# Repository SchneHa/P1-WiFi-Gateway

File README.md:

### P1-WiFi-Gateway
P1-WiFi-Gateway mit Unterstützung der cFos Power Brain Wallbox

P1 wifi gateway 2022

**(English Version below)**

Basierend auf einem Repo von Ronald Leenes: https://github.com/romix123/P1-wifi-gateway

Diese Software vereint verschiedene Komponenten in einem handlichen Paket.
Die Software läuft auf einem ESP8266 board wie dem Wemos D1 mini oder mini Pro und hat einen bescheidenen Platzbedarf.

Die Datenverarbeitung basiert auf: http://domoticx.com/p1-poort-smart-meter-data-to-domoticz-esp8266 
Das Captive Portal basiert auf einem der ESP8266-Beispiele, die OTA-Einheit ebenfalls.

Das Modul liefert Daten über JSON- oder MQTT-Nachrichten an einen Host, kann aber auch über das Webinterface des Moduls oder per Telnet ausgelesen werden. Die Daten können an einen virtuellen Zähler "HTTP input" in der Power Brain Wallbox von cFos übertragen werden und dort für das Lastmanagement genutzt werden. Damit das funktioniert, muss der Charging Manager der Wallbox mindestens auf die Firmwareversion 1.17.4-beta gebracht werden.

Das Modul lädt beim Start zuerst den Pufferkondensator auf. Es blinkt dann 2x und versucht zunächst, sich mit Ihrem WLAN-Netzwerk zu verbinden. Während dieses Vorgangs blinkt die LED mit einer Periode von 0,5 Hz. Kommt keine Verbindung zustande, startet das Modul einen Access Point mit dem Namen P1_Setup. Verbinden Sie sich mit diesem Netzwerk und surfen Sie zu 192.168.4.1

Daraufhin erscheint der Menübildschirm des Moduls. Geben Sie dort die SSID und das Passwort Ihres WLAN-Netzwerks ein. Darunter tragen Sie die Daten des empfangenden Servers (IP und Portnummer) ein. Dies kann Ihr Domotociz-Server sein, in diesem Fall müssen Sie auch die IDx eingeben, die Domoticz für ein Gas- und ein Energiegerät erstellt. 
Auch die Daten für einen (z. B. auf einem Raspberry Pi selbst gehosteten) MQTT-Broker können jetzt eingegeben werden.

Wenn die Daten für das Lastmanagement einer cFos Power Brain Wallbox genutzt werden sollen, ist dies ebenfalls hier möglich.

In der jetzt veröffentlichten Version 1.2f ist es nun auch möglich, Gas-Verbrauchswerte über MQTT zu empfangen, die von einem Gassensor wie in meinem Repo https://github.com/SchneHa/Gas_Meter beschrieben gesendet werden. Es werden im Webinterface des P1-Gateways der Gas-Gesamtzähler und der aktuelle Tageszähler dargestellt. Dafür kann derselbe Broker wie für die anderen Werte angegeben werden, es kann aber auch ein anderer Broker sein.

Schließlich geben Sie an, wie viele Sekunden Daten an den Server gesendet werden sollen. DSMR4-Messgeräte verwenden ein Messintervall von 10 Sekunden. SMR5-Zähler liefern jede Sekunde Daten. Das erscheint  viel und das Modul benötigt auch viel Strom, daher ist die Frage, ob es parasitär (powered by the meter) arbeiten kann. Empfohlen ist  ein Intervall von 15 Sekunden oder höher. Das hier eingegebene Intervall wird nicht immer synchron zum Datenintervall des Zählers sein, gehen Sie also nicht davon aus, dass Sie in Domoticz, MQTT oder im Charging Manager der cFos Wallbox  genau alle x Sekunden einen Messwert sehen. 

Das Modul „schläft“ zwischen den Messungen (das Modem wird ausgeschaltet, so dass die Stromaufnahme von ca. 70 mA auf 15 mA sinkt). Dies gibt dem Pufferkondensator Zeit, sich für die vom WLAN-Sender des Moduls erzeugten Stromspitzen aufzuladen (und es spart dennoch etwas Strom (der von Ihrem Energieversorger bezahlt wird, aber trotzdem)). Jedes bisschen hilft.

Siehe http://esp8266thingies.nl für weitere Informationen über das Modul und http://www.esp8266thingies.nl/wp/forum-2/ für das Diskussionsforum.

Ergänzung vom 31.07.2023: Seit heute sind die PCB Dateien im KiCAD Format online. Das Board wurde schon produziert und getestet. Ebenso stehen die Gerber Dateien zur Verfügung.

Ich habe noch einige PCBs aus der ersten Produktion übrig, bei Bedarf bitte melden.
```
PCB unbestückt: 5€
PCB mit Bauteilen: 10€
PCB fertig bestückt: 15€
D1 mini ESP8266 mit Headern: 10€
inklusive Versand innerhalb Deutschlands
hans(dot)schneider(at)gmx(dot)ch
```

```
Version: 1.2f Datum: 29. Mai 2026
         Gasverbrauch (Gesamtzähler und Tageszähler), Import der Werte über MQTT implementiert
         Voraussetzung: Vorhandensein eines Gas-Sensors wie unter meinem Repo
         https://github.com/SchneHa/Gas_Meter beschrieben
Version: 1.2e Datum: 02.11.2025
         Checkt nun in jedem loop, ob eine Verbindung zum WiFi besteht. Wenn nicht, wird die
         Verbindung neu hergestellt.
Version: 1.2d Datum: 15.01.2025
         nach Ändern des voreingestellten Passworts für die cFos Power Brain wird das Passwort
         nun nicht mehr vergessen
Version: 1.2c Datum: 23.05.2024
         die Anzeige der Seite mit den Messwerten wird nun alle 20 Sekunden erneuert
         P1meter sendet nun positive Werte für actualElectricityPowerDelivered und negative Werte
         für actualElectricityPowerReturned zur cFos Power Brain Wallbox (das ist wichtig um
         korrekte Werte für die Einspeisung ins Stomnetz zu erhalten)
Version: 1.2b Datum: 22.05.2023
         Anpassungen für die Firmware 1.19.4 der cFos Power Brain Wallbox
         (power_va ist nun power_w, is_va existiert nicht mehr)
         Korrekturen der niederländischen, französischen und schwedischen Version
Version: 1.2a Datum: 13.03.2023
         Fertigstellung der französischen und schwedischen Version
         diverse Verbesserungen und Fehlerbehebungen
Version: 1.2 Datum: 05.03.2023, Autor: Hans Schneider
         Unterstützung für den HTTP_input Zähler der cFos Power Brain Wallbox hinzugefügt
         diverse Verbesserungen und Fehlerbehebungen
Version: 1.1adc Datum: 12.02.2023 Autor: Ronald Leenes
1.1adc: Umfangreiche Protokollierung implementiert
        Schwedische Version aktualisiert, um sie an die niederländische Version anzugleichen 
        (Deutsche und Französische Version haben keine Sicherheitsfunktionen bei Setup/Update)
1.1aa: Fehlerkorrekturen 1.1: Graphen implementiert BerichtstarifIndicatorElectricity behoben
ud: Kopfzeilen aktualisieren behoben ua: Problem mit Setup-Feldern behoben
u: Passwortschutz für Setup- und Update-Firmware-Menüs hinzugefügt
   Gehen Sie beim ersten Booten von Version 1.0u innerhalb von 60 Sekunden zum Setup-Menü, um den
   Passwortschutz zu umgehen
   Out-of-the-Box-Unterstützung für die Integration von Home Assistant "DSMR Reader" hinzugefügt 
   Verwenden Sie „dsmr“ als MQTT-Präfix und Daten werden automatisch im „DSMR Reader“-Format an den
   MQTT-Broker geliefert
   MQTT-Wiederverbindung behoben, es ist jetzt nicht blockierend
   Zurücksetzen der Hardboot-Tageszähler behoben
   Senden leerer MQTT-Nachrichten behoben
   Insgesamt verbesserte Stabilität
t: Verbesserungen bei der Energieverwaltung
   allgemeine (kleinere) Bereinigung
ta: Korrektur für Telnet-Berichte
    französische Lokalisierung hinzugefügt
s: deutsche Lokalisierung hinzugefügt 
   mqtt-Ausgabe für schwedische spezifische OBIS-Codes hinzugefügt
r: Geschwindigkeitsverbesserungen und Rationalisierung der Parser-Lokalisierungen für: NL, SE
q: Tageswerte hinzugefügt 
p: EquipmentID in mqtt set eingebaut 
o: fixe Gasleistung, fixes mqtt reconnect 
n: leerer Aufruf von SetupSave leitet jetzt zum Hauptmenü weiter statt Einstellungen zurückzusetzen ;-)
   behobene kWh/Wh Invertierung 
m: setupsave fix, relocate to p1wifi.local nach 60 Sek. mqtt 
   kw/W fix 
l: wifireconnect nach WLAN-Verlust 
k: großer BUG behoben, SoftAP würde keinen erreichbaren Webserver erzeugen 
j: Rohdaten auf Port 23
   Hauptcodeumschreibung 
   implementierte Datenberichtsmethoden: geparste Daten: json, mqtt, p1wifi.local/P1 
   Rohdaten: Telnet auf Port 23, p1wifi.local/Data
i: erweiterte maximale Leitungslänge für TD210-D-Zähler, die eine wirklich lange 1-0:99.97.0-Leitung haben 
h: erweitertes mqtt-Set mit sofortigen Leistungen, Spannungen, aktueller Tarifgruppe 
   Stromausfälle, Stromabfälle 
g: feste mqtt
```

Empfohlenes Board:

Wemos D1 mini Pro, Flash Größe: 16 MB, FS: 14 MB, OTA: ~1019 kB

ebenso möglich:

Wemos D1 R2 & mini, Flash Größe: 4 MB, FS: 2 MB, OTA: ~1019 kB oder jedes andere kompatible board

```
Benötigte Dateien:
  P1WG2022current.ino
  CRC16.h 
  JSON.ino 
  MQTT.ino 
  TELNET.ino 
  debug.ino 
  decoder.ino 
  functions.ino 
  graph.ino
  logging.ino
  vars.h
  webserver.ino
  webserverDE.ino
  webserverFR.ino
  webserverNL.ino
  webserverSE.ino
  wifi.ino
```
Anmerkung: <Del>Zurzeit sind nur die deutsche und die niederländische Versionen lauffähig.</Del> Bei der französischen und der schwedischen Version muss ggf. die Übersetzung korrigiert werden.

**English Version:**

P1-WiFi-Gateway with support for cFos Power Brain Wallbox

P1 wifi gateway 2022

Based on a repo of Ronald Leenes: https://github.com/romix123/P1-wifi-gateway

This software combines various components in one handy package.
The software runs on an ESP8266 board like the Wemos D1 mini or mini Pro and has a modest footprint.

The data processing is based on: http://domoticx.com/p1-poort-smart-meter-data-to-domoticz-esp8266
The captive portal is based on one of the ESP8266 samples, as is the OTA unit.

The module delivers data to a host via JSON or MQTT messages, but can also be read out via the module's web interface or via Telnet. It is possible to send data to a virtual meter "HTTP input" of the Power Brain Wallbox of cFos which can be used to implement load management. For that to work Charging Manager of cFos Power Brain Wallbox has to be at least on firmware version 1.17.4-beta.

When starting, the module first charges the buffer capacitor. It will then blink 2x and first try to connect to your WiFi network. During this process, the LED flashes with a period of 0.5 Hz. If no connection is established, the module starts an access point with the name P1_Setup. Connect to this network and surf to 192.168.4.1

The module menu screen appears. Enter the SSID and password of your WiFi network there. Below this, enter the data of the receiving server (IP and port number). This can be your Domotociz server, in this case you also have to enter the IDx that Domoticz creates for a gas and an energy device.
The data for an MQTT broker (e.g. hosted on a Raspberry Pi itself) can now also be entered.

If the data is to be used for load management of a cFos Power Brain Wallbox, this is also possible here.

In the newly released version 1.2f, it is now also possible to receive gas consumption data via MQTT, sent by a gas sensor as described in my repository https://github.com/SchneHa/Gas_Meter. The total gas meter reading and the current daily meter reading are displayed in the P1 gateway's web interface. The same broker used for the other values ​​can be specified for this, or a different broker can be used.

Finally, specify how many seconds of data should be sent to the server. DSMR4 gauges use a measurement interval of 10 seconds. SMR5 counters provide data every second. That seems a lot to me and the module also draws a lot of current, so the question is whether it can operate parasitically (powered by the meter). I recommend an interval of 15 seconds or higher. The interval entered here will not always be in sync with the meter's data interval, so don't assume that you will see a reading in Domoticz, MQTT or in Charging Manager of the cFos Wallbox exactly every x seconds. 

The module "sleeps" between the measurements (the modem is switched off so that the current consumption drops from approx. 70 mA to 15 mA). This gives the buffer capacitor time to charge up for the current spikes generated by the module's WiFi transmitter (and it still saves some electricity (which is paid for by your utility, but still)). Every little helps.

See http://esp8266thingies.nl for more information about the module and http://www.esp8266thingies.nl/wp/forum-2/ for the discussion forum.

Addition from 07/31/2023: Since today the PCB files in KiCAD format are online. The board has already been produced and tested. The Gerber files are also available.

I still have some PCBs left from the first batch, please let me know if you need one.

```
PCB unassembled: 5€
PCB with parts: 10€
PCB assembled: 15€
D1 mini ESP8266 with headers: 10€
shipping to Germany included
hans(dot)schneider(at)gmx(dot)ch
```

```
Version: 1.2f Date: 29.5.2026
         Gas consumption (Total counter and daily counter), import of the values via MQTT implemented
         Requirement: A Gas sensor as described in my repo https://github.com/SchneHa/Gas_Meter must
         be available
Version: 1.2e Date: 02.11.2025
         now checks connection to wifi in every loop, if not connected it will be reconnected
Version: 1.2d Date: 15.01.2025
         after changing cFos Power Brain password from it's default the new password isn't forgotten anymore now
Version: 1.2c Date: 23.05.2024
         measurement page refreshes every 20 seconds now
         P1meter now sends positive values for actualElectricityPowerDelivered and negative values for
         actualElectricityPowerReturned to cFos Power Brain wallbox (that is important to calculate correct
         values for feeding energy into the power grid)
Version: 1.2b Date: 22.05.2023
         changes for cFos Power Brain Firmware 1.19.4
         (power_va is now power_w, is_va doesn't exist anymore)
         improvements of dutch, french and swedish language
Version: 1.2a Date: 13.03.2023
         Finishing the french and swedish Version
         various Improvements and bug fixes
Version: 1.2 Date: 03/05/2023, Author: Hans Schneider
         added Support for the HTTP_input meter of cFos Power Brain Wallbox
         various improvements and bug fixes
Version: 1.1adc Date: 02/12/2023 Author: Ronald Leenes
1.1adc: Extensive logging implemented
        Swedish version updated to match Dutch version 
        (German and French versions have no security features on setup/update)
1.1aa: Bug fixes 1.1: Graphs implemented
       Reporting TariffIndicatorElectricity fixed
ud: fixed update headers 
ao: fixed problem with setup fields
u: Added password protection for setup and update firmware menus when booting version 
1.0u for the first time, go to setup menu within 60 seconds to bypass password protection
     Added out-of-the-box support for Home Assistant "DSMR Reader" integration 
     Use "dsmr" as MQTT prefix and data is automatically delivered to the MQTT broker in "DSMR Reader" format
     Fixed MQTT reconnection, it's non-blocking now
     Fixed resetting hardboot day counters
     Fixed sending empty MQTT messages
     Improved overall stability
t: Power management improvements
   general (minor) cleanup 
ta: Fix for telnet reports
    added French localization
s: added german localization
   added mqtt output for swedish specific OBIS codes
r: Speed improvements and streamlining of parser 
   localizations for: NL, SE
q: daily values added 
p: EquipmentID built into mqtt set 
o: fixed gas power
   fixed mqtt reconnect 
n: empty call to SetupSave now redirects to main menu instead of resetting settings ;-)
   fixed kWh/Wh inversion 
m: setupsave fix, relocate to p1wifi.local after 60 sec. 
   mqtt - kw/W fix 
l: wifi reconnect after WLAN loss 
k: major BUG fixed
   SoftAP would not create an accessible web server 
j: raw data on port 23 
   main code rewrite
   implemented data reporting methods: parsed data: json, mqtt, p1wifi.local/P1 
   raw data: telnet on port 23, p1wifi.local/Data
i: extended maximum line length for TD210-D meters that have a really long 1-0:99.97.0 line 
h: extended mqtt set with instantaneous powers, voltages, current tariff group
   blackouts, blackouts 
g: fixed mqtt
```

Recommended board:

Wemos D1 mini Pro, Flash Größe: 16 MB, FS: 14 MB, OTA: ~1019 kB

also possible:

Wemos D1 R2 & mini, Flash Größe: 4 MB, FS: 2 MB, OTA: ~1019 kB or any other compatible board

Files needed:
```
  P1WG2022current.ino
  CRC16.h
  JSON.ino
  MQTT.ino
  TELNET.ino
  debug.ino
  decoder.ino
  functions.ino
  graph.ino
  logging.ino
  var.h
  webserver.ino
  webserverDE.ino
  webserverFR.ino
  webserverNL.ino
  webserverSE.ino
  wifi.ino
```

Note: <Del>Only the German and Dutch versions are currently working.</Del> The French and the Swedish version needs improvement of translation.

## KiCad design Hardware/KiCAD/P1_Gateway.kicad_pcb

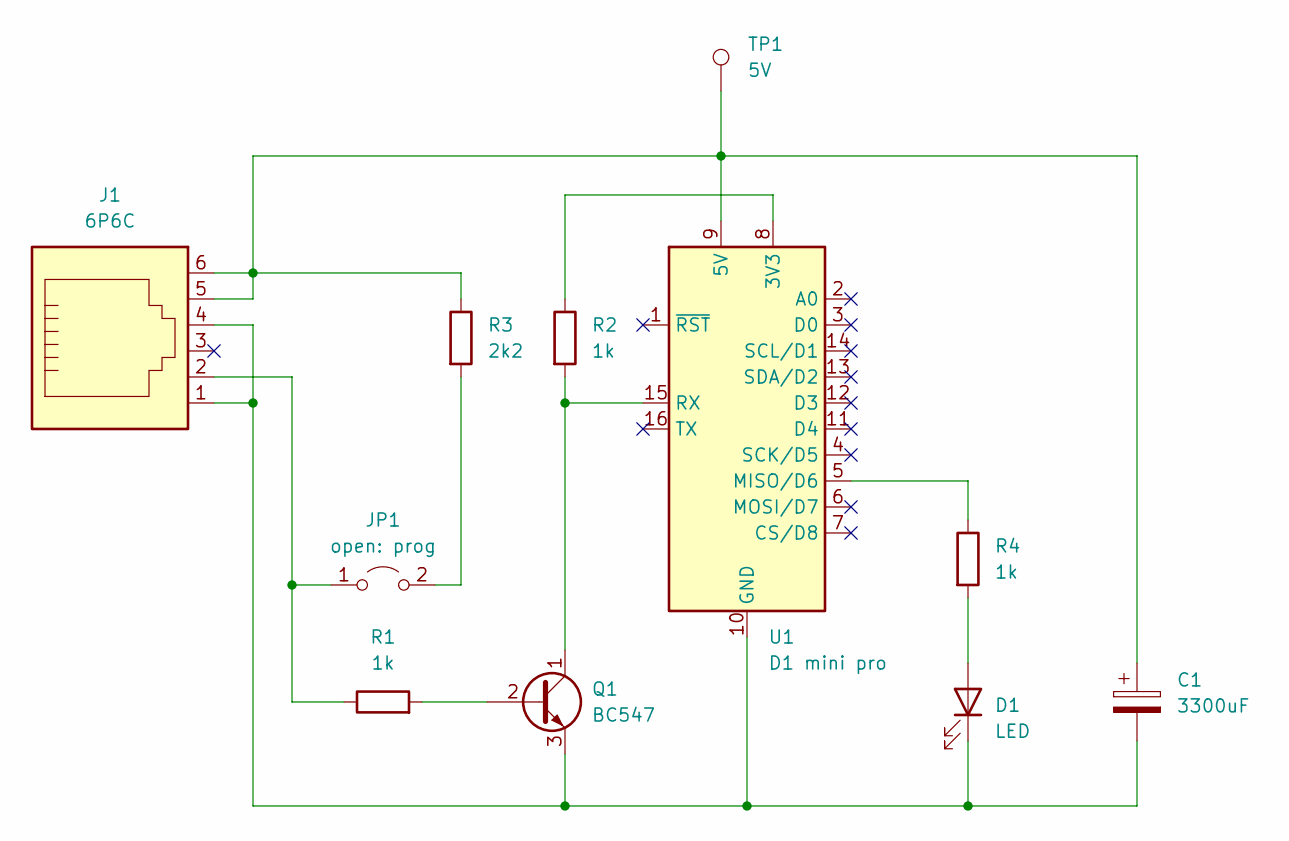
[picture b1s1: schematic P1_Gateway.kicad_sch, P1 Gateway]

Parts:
C1: 3300uF; CP_Radial_D5.0mm_P2.50mm
D1: LED; LED_D3.0mm
J1: 6P6C; RJ12_Amphenol_54601
JP1: open: prog; TestPoint_2Pads_Pitch2.54mm_Drill0.8mm
Q1: BC547; TO-92L_Inline_Wide
R1, R2, R4: 1k; R_Axial_DIN0204_L3.6mm_D1.6mm_P7.62mm_Horizontal
R3: 2k2; R_Axial_DIN0204_L3.6mm_D1.6mm_P7.62mm_Horizontal
TP1: 5V; TestPoint_Keystone_5000-5004_Miniature
U1: D1 mini pro; WEMOS_D1_mini_light

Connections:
unnamed: C1.1, J1.5, J1.6, R3.1, TP1.1, U1.9 (5V)
unnamed: C1.2, D1.1 (K), J1.1, J1.4, Q1.3 (E), U1.10 (GND)
unnamed: D1.2 (A), R4.2
unnamed: J1.2, JP1.1 (A), R1.1
unnamed: JP1.2 (B), R3.2
unnamed: Q1.1 (C), R2.2, U1.15 (RX)
unnamed: Q1.2 (B), R1.2
unnamed: R2.1, U1.8 (3V3)
unnamed: R4.1, U1.5 (MISO/D6)

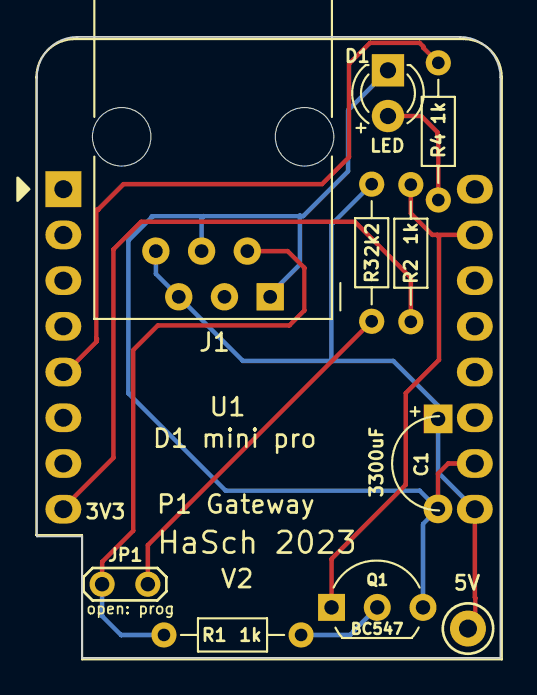
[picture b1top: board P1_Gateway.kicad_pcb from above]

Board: 2 copper layers, 25.8 x 34.5 mm, 11 parts (0 on the bottom side), 9 nets.

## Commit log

2023-05-18 Update P1WG2022current.ino
    Fixed a bug that prevents starting webservices
2023-05-19 Update P1WG2022current.ino
    bug fixes
2023-05-19 Bug fixes
2023-05-20 version 1.2ab
    (re)activated display of module voltage in footer of webserver pages, bug fixes
2023-05-21 display of module voltage (re)activated
2023-05-22 Changes for cFos Power Brain FW 1.19.4
    power_va is now power_w, is_va doesn't exist anymore in FW 1.19.4
    improvements of Netherlands, French and Swedish language
2023-07-31 Update README.md
    Addition: PCB files ready!
2024-05-09 4
    Now, measurements page refreshes every 20 seconds
2024-05-09 12
    actual firmwares updated
2024-05-14 10
    P1meter now sends positive values for actualElectricityPowerDelivered and negative values for actualElectricityPowerReturned to cFos Power Brain wallbox
2024-05-14 3
    cosmetic changes
2024-05-14 Update README.md
    changes in version 1.2c
2024-05-14 24
    actual firmwares
2024-05-17 2
    now, power_w in cFos Power Brain is displayed correctly
2024-05-19 2
    fixing an annoying bug: now, actualElectricityPowerReturned is handled correctly using cFos wallbox
2024-05-19 Update JSON.ino
    deleting lines inserted for debugging purposes
2024-05-20 2
    bug fixing
2024-05-21 Update JSON.ino
    bug fixing
2024-05-25 12
    firmware updated
2025-01-15 cFos user password issue
    after changing cFos Power Brain password from it's default the new password isn't now forgotten anymore
2025-11-02 13
    Now checks wifi connection during loop
2026-01-26 Update version to 1.2e and enhance WiFi checks
    Updated version information and added functionality details regarding WiFi connection checks.
2026-01-26 Update WiFi connection check description in README
2026-01-28 Format README.md for better readability
2026-01-28 Update README to remove language version note
    Removed note about language versions from the README.
2026-01-28 Check softAP status before WiFi connection check
2026-01-28 Update links to point to GitHub repository
2026-01-28 Fix variable name case for softAP in condition
2026-01-28 Update firmwares
2026-06-10 Changes mainly for MQTT Gas
2026-06-10 Update README with gas consumption feature details
    Added information about gas consumption data reception via MQTT in version 1.2f.
2026-06-10 Firmwares 1.2f updated
2026-06-13 Clarify comment on gas topic comparison
    Updated comment for clarity on gas topic comparison.
